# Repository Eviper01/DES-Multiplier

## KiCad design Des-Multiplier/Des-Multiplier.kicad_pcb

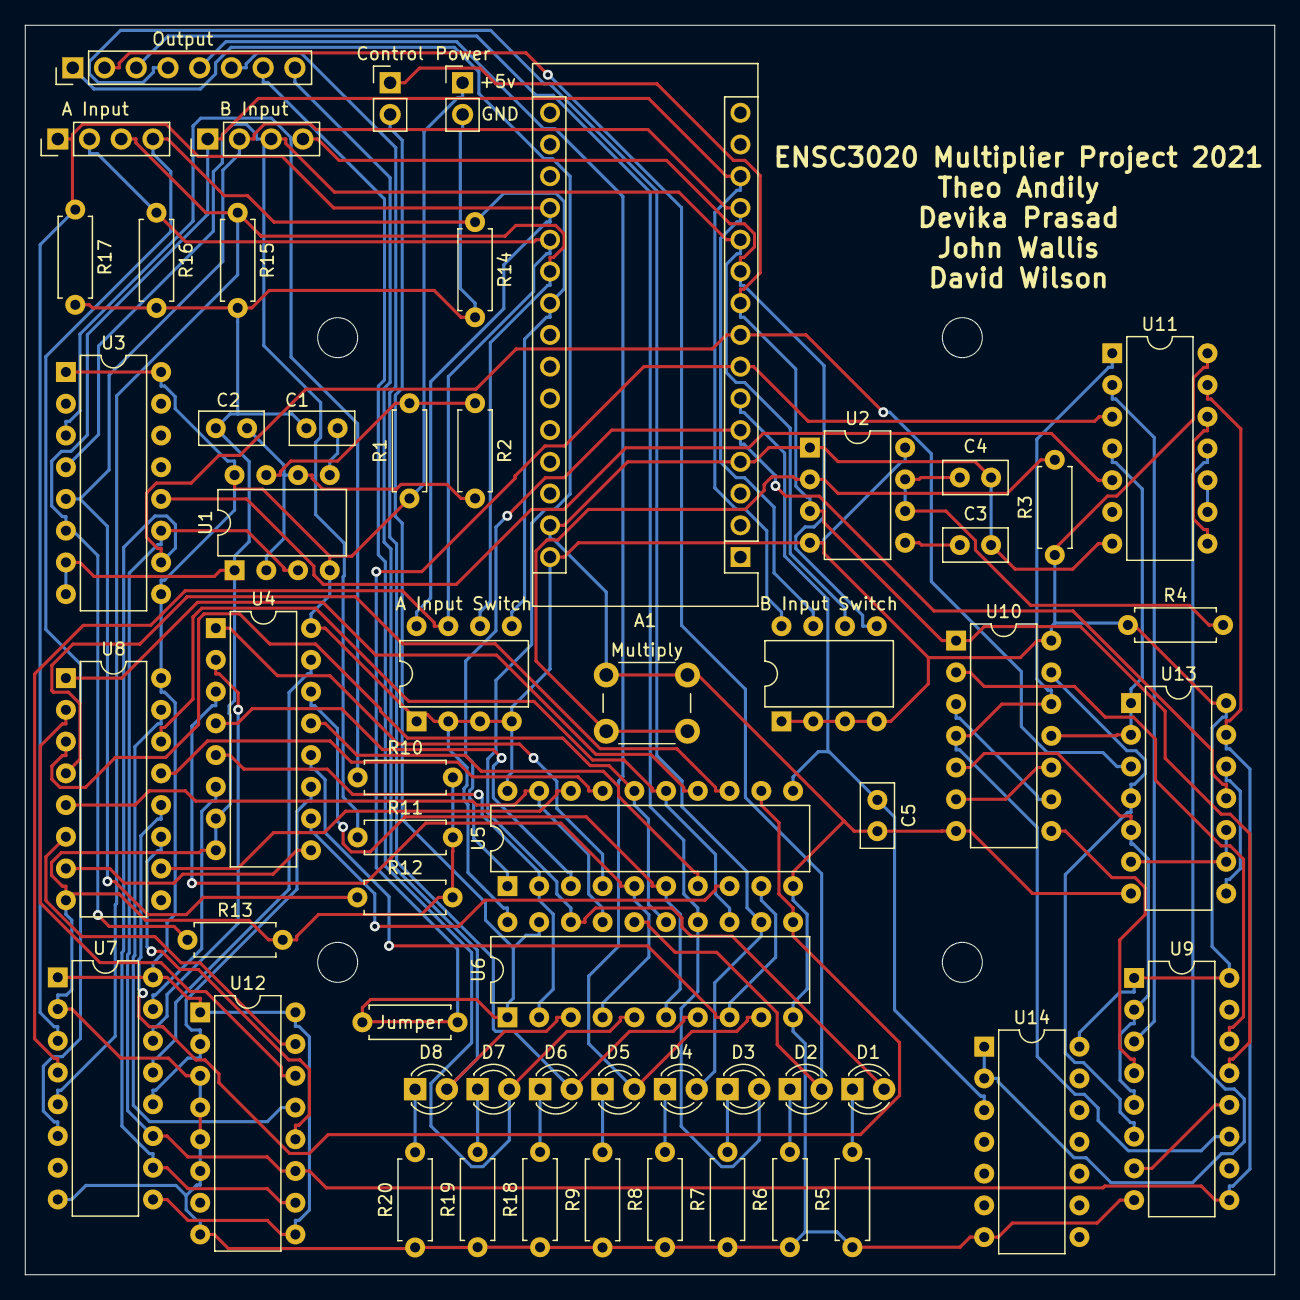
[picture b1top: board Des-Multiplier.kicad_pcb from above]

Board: 2 copper layers, 100.0 x 100.0 mm, 61 parts (0 on the bottom side), 80 nets.

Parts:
A1: Arduino_Nano_Every; Arduino_Nano
A Input: Conn_01x04_Male; PinHeader_1x04_P2.54mm_Vertical
A Input Switch: SW_DIP_x04; DIP-8_W7.62mm
B Input: Conn_01x04_Male; PinHeader_1x04_P2.54mm_Vertical
B Input Switch: SW_DIP_x04; DIP-8_W7.62mm
C1, C2, C3, C5: 10n; C_Disc_D5.0mm_W2.5mm_P2.50mm
C4: 100n; C_Disc_D5.0mm_W2.5mm_P2.50mm
Control: Conn_01x02_Male; PinHeader_1x02_P2.54mm_Vertical
D1, D2, D3, D4, D5, D6, D7, D8: LED; LED_D3.0mm
Jumper: R; R_Axial_DIN0207_L6.3mm_D2.5mm_P7.62mm_Horizontal
Multiply: SW_Push; SW_PUSH_6mm
Output: Conn_01x08_Male; PinHeader_1x08_P2.54mm_Vertical
Power: Conn_01x02_Male; PinHeader_1x02_P2.54mm_Vertical
R1, R2, R3, R10, R11, R12, R13, R14, R15, R16, R17: 1K; R_Axial_DIN0207_L6.3mm_D2.5mm_P7.62mm_Horizontal
R4: 1M; R_Axial_DIN0207_L6.3mm_D2.5mm_P7.62mm_Horizontal
R5, R6, R7, R8, R9, R18, R19, R20: 330; R_Axial_DIN0207_L6.3mm_D2.5mm_P7.62mm_Horizontal
REF1, REF2, REF3, REF4: MountingHole_3.2mm_M3
U1, U2: NE555P; DIP-8_W7.62mm
U3, U7, U12: 74LS194; DIP-16_W7.62mm
U4, U8: 74LS283; DIP-16_W7.62mm
U5: 74LS273; DIP-20_W7.62mm
U6: 74LS244; DIP-20_W7.62mm
U9: 74LS175; DIP-16_W7.62mm
U10, U11, U13, U14: 74HC00; DIP-14_W7.62mm

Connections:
+5V: A1.30, A Input Switch.1, A Input Switch.2, A Input Switch.3, A Input Switch.4, B Input Switch.1, B Input Switch.2, B Input Switch.3, B Input Switch.4, Power.1, R1.1, R3.1, R4.1, U1.4, U1.8, U2.4, U2.8, U3.1, U3.9, U3.16, U4.16, U5.20, U6.20, U7.1, U7.9, U7.16, U8.16, U9.1, U9.16, U10.14, U11.14, U12.1, U12.9, U12.16, U13.14, U14.14
/A0: A1.13, B Input.1, B Input Switch.8, R13.1, U3.6
/A1: A1.12, B Input.2, B Input Switch.7, R12.1, U3.5
/A2: A1.11, B Input.3, B Input Switch.6, R11.1, U3.4
/A3: A1.10, B Input.4, B Input Switch.5, R10.1, U3.3
/Acc0: U4.5, U5.2, U6.2
/Acc1: U4.3, U5.5, U6.4
/Acc2: U4.14, U5.6, U6.6
/Acc3: U4.12, U5.9, U6.8
/Acc4: U5.12, U6.11, U8.12
/Acc5: U5.15, U6.13, U8.14
/Acc6: U5.16, U6.15, U8.3
/Acc7: U5.19, U6.17, U8.5
/AccCLK: A1.6, C5.1, U5.11, U14.3
/Acc_Load_En: U10.11, U11.4, U13.1, U13.2
/Astatus: U3.12, U11.5
/B0: A1.19, A Input.1, A Input Switch.8, R17.1, U7.3
/B1: A1.20, A Input.2, A Input Switch.7, R16.1, U7.4
/B2: A1.21, A Input.3, A Input Switch.6, R15.1, U7.5
/B3: A1.22, A Input.4, A Input Switch.5, R14.1, U7.6
/Bout0: U4.6, U7.15
/Bout1: U4.2, U7.14
/Bout2: U4.15, U7.13
/Bout3: U4.11, U7.12, U12.2
/Bout4: U8.6, U12.15
/Bout5: U8.2, U12.14
/Bout6: U8.15, U12.13
/Bout7: U8.11, U12.12
/CLK: U1.3, U3.11, U7.11, U9.9, U11.13, U12.11, U13.13
/Go: A1.9, Control.1, U2.3, U9.13, U10.1
/Load: U11.8, U11.12
/Out0: D1.2, Output.1, U6.18
/Out1: D2.2, Output.2, U6.16
/Out2: D3.2, Output.3, U6.14
/Out3: D4.2, Output.4, U6.12
/Out4: D5.2, Output.5, U6.9
/Out5: D6.2, Output.6, U6.7
/Out6: D7.2, Output.7, U6.5
/Out7: D8.2, Output.8, U6.3
/PreState0: U9.4, U10.8
/ResetFlag: U13.8, U13.12
/State0: U9.2, U9.5, U10.5, U13.5
/State1: U9.7, U9.12
/~AccCLK: U11.11, U14.1, U14.2
/~Ashift~\Load: A1.8, U3.10, U7.10, U12.10, U13.3
/~DSP: A1.7, Jumper.2, U11.3
/~DSP1: Control.2, Jumper.1, U6.1, U6.19
/~GoDetect: U9.14, U10.2
/~GoEdge: U10.3, U10.9
/~Load: U11.9, U11.10
/~Q1~nQ0: U13.6, U13.9, U13.10
/~Reset: A1.5, U5.1, U13.11
/~S2~nQ0: U10.6, U10.10
/~State0: U9.3, U11.2
/~State1: U9.6, U10.13, U13.4
/~State2: U9.11, U10.4, U10.12, U11.1
GND: A1.4, A1.29, C1.2, C2.2, C3.2, C4.2, C5.2, Multiply.1, Power.2, R5.1, R6.1, R7.1, R8.1, R9.1, R10.2, R11.2, R12.2, R13.2, R14.2, R15.2, R16.2, R17.2, R18.1, R19.1, R20.1, U1.1, U2.1, U3.7, U3.8, U4.7, U4.8, U5.10, U6.10, U7.2, U7.8, U8.8, U9.8, U10.7, U11.7, U12.3, U12.4, U12.5, U12.6, U12.8, U13.7, U14.7
unnamed: C1.1, U1.5
unnamed: C2.1, R2.2, U1.2, U1.6
unnamed: C3.1, U2.5
unnamed: C4.1, R4.2, U2.6, U2.7
unnamed: D1.1, R5.2
unnamed: D2.1, R6.2
unnamed: D3.1, R7.2
unnamed: D4.1, R8.2
unnamed: D5.1, R9.2
unnamed: D6.1, R18.2
unnamed: D7.1, R19.2
unnamed: D8.1, R20.2
unnamed: R1.2, R2.1, U1.7
unnamed: Multiply.2, R3.2, U2.2
unnamed: U4.1, U5.4
unnamed: U4.4, U5.3
unnamed: U4.9, U8.7
unnamed: U4.10, U5.8
unnamed: U4.13, U5.7
unnamed: U5.13, U8.4
unnamed: U5.14, U8.1
unnamed: U5.17, U8.13
unnamed: U5.18, U8.10

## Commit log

2021-09-07 Functional Units and CLK
2021-09-08 added state machine based timing control
2021-09-09 timing diagram
2021-09-13 updating logic symbols
2021-09-16 pcb production beigns
2021-09-16 pcb layout draft
2021-09-17 board changes
2021-09-20 mounting hole respins
